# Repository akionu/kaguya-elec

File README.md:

# kaguya-elec

CanSatのための小型電装基板です。第19回能代宇宙イベント出場機体『かぐや』（同志社大学）のために作りました。

- 大幅な小型化を実現しました（当団体比）。42x25mmでここまでできる！
- 安定して動作しています。
- 50mから自由落下しても故障しませんでした（投下1回目）。

ブロック図：

中身としては、RP2040を中心に、電源(DCDC)、無線（LoRa）、センサー（9軸IMU・気圧）、外付けセンサー用コネクタ（GPS・ToF測距）といった感じです。なお、モータードライバは別の基板として分離して使うようにしてあります。

回路図（詳しくはKiCadのデータを参照）：

アートワーク：
表：

裏：

## 『かぐや』について

第19回能代宇宙イベント出場機体『かぐや』（同志社大学）の基板です。
この機体の特徴：
- 成功率向上のため、2機体投下
    - タテに二つ重ねて投下するのでなく、制御性向上のため、ヨコに2つ並べてキャリアに収納
    - そのためのタイヤ展開
- 小型の基板

3回投下した中で、投下2回目の7mが最良の結果でした。実際の状況は大会報告書を参照されたいですが、走破性の不足によるスタックが一番の問題でした（3回ともプログラムは正常に動作・ログ取得）。
- 機体：運営特別賞
- ポスター：能代ロケット実験場　所長賞

なお、この基板で動かしたコードもGitHub上で公開しています。
[リンク](https://github.com/Yudetamago-AM/kaguya-code)

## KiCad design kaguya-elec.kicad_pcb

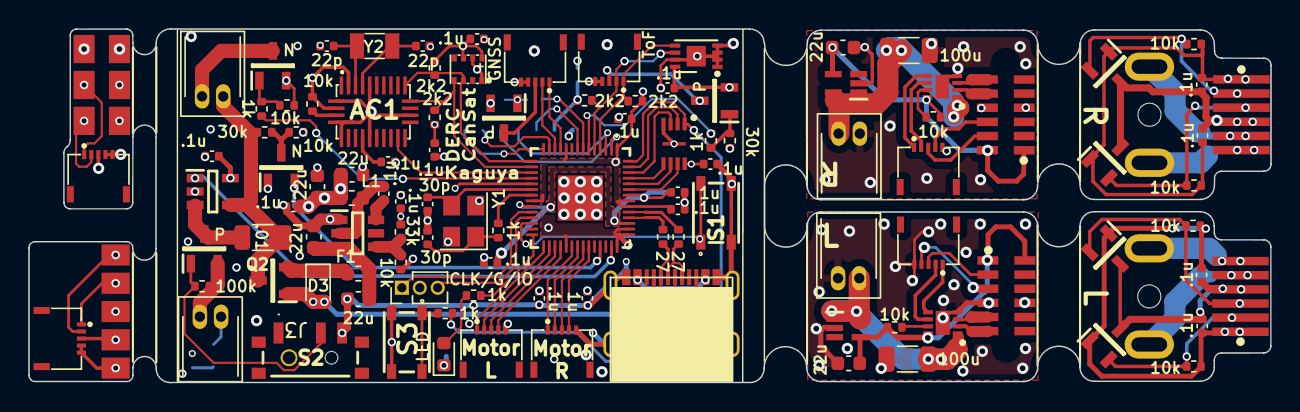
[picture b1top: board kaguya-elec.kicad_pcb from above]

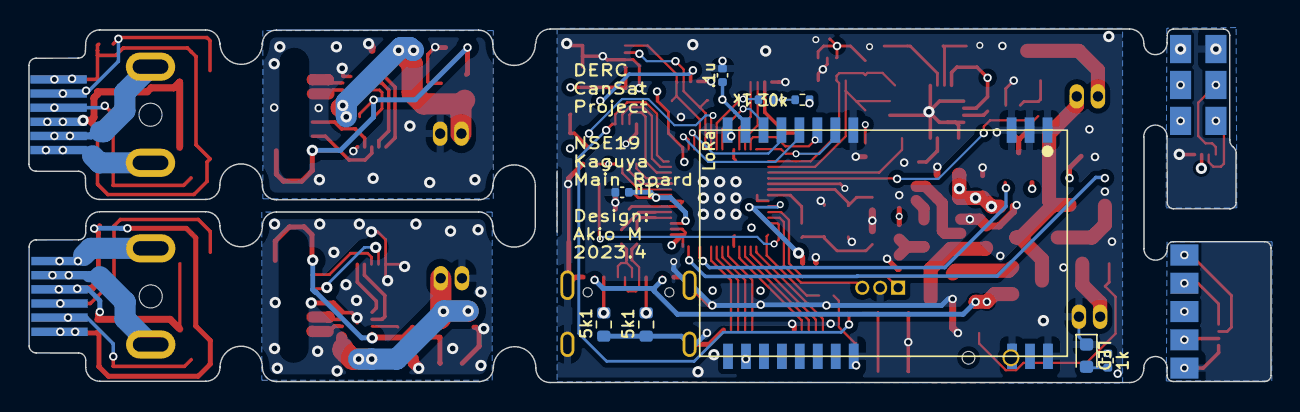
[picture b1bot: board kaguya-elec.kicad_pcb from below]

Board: 4 copper layers, 87.9 x 25.0 mm, 118 parts (9 on the bottom side), 84 nets.

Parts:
AC1: BNO085
C1, C2, C5, C6, C7, C8, C11, C12, C13, C14, C17, C18, C20, C22, C24, C25, C28, C35, C36: 100n; C_0402_1005Metric
C3, C4: 30p; C_0402_1005Metric
C9, C10: 1u; C_0402_1005Metric
C15, C16, C26, C27, C29, C34: 22u; C_0603_1608Metric
C19, C30: 100u; C_1206_3216Metric
C21, C23: 22p; C_0402_1005Metric
D1, D2: LED; LED_0603_1608Metric
D3: CUS10S30; D_SOD-323
F1: BSMD0603-050-9V; Fuse_0603_1608Metric
IC1: RP2040; RP2040TR7
IC2: W25Q16JVUXIQ; SON50P300X200X60-9N
IC3: M24512-DFMC6TG; DFN-8-1EP_3x2mm_P0.5mm_EP1.36x1.46mm
IC4: INA180A2IDBVR; SOT95P280X145-5N
IC5: AP62300TWU-7; SOT95P280X100-6N
IC6, IC11: NJM2878F3-33-TE2; SOT65P210X100-5N
IC7, IC8, IC9, IC10: DRV5013ADQDBZR; SOT95P237X112-3N
IC12, IC14: DRV8837DSGR; SON50P200X200X80-9N
J1: Debug Port; PinHeader_1x03_P1.27mm_Vertical
J2, J3, J10, J15: JST ZH 2; JST ZH 2 Side
J4: ToF; HC-FPC-05-10-5RLTAG
J5: GNSS; HC-FPC-05-10-5RLTAG
J6, J13: B2BL; HC-FPC-05-10-5RLTAG
J7, J14: B2BR; HC-FPC-05-10-5RLTAG
J8: encoderR; encoder connector p-side
J9: encoderL; encoder connector p-side
J11: encoderR; encoder connector e-side
J12: encoderL; encoder connector e-side
J16: ToF_C_P; HC-FPC-05-10-5RLTAG
J17: ToF_C_T; ToF_Flat2
J18: GNSS_C_P; HC-FPC-05-10-5RLTAG
J19: GNSS_C_T; GNSS_Flat
L1: 3.3u; L_0603_1608Metric
M1: Motor_DC_R; motor
M2: Motor_DC_L; motor
Q1, Q4: IRFML8244TRPBF; SOT95P237X112-3N
Q2, Q3, Q5, Q6: IRLML6402; SOT95P237X112-3N
R1, R2, R3, R9, R10, R30, R31: 1k; R_0402_1005Metric
R4, R14, R19, R23, R24, R25, R26, R27, R28, R29: 10k; R_0402_1005Metric
R5, R6: 5.1k; R_0603_1608Metric
R7, R8: 27; R_0402_1005Metric
R11, R12, R15, R16: 2k2; R_0402_1005Metric
R13: 100k; R_0402_1005Metric
R17: 0.01; R_1206_3216Metric
R18, R21, R22: 30k; R_0402_1005Metric
R20: 33.2k; R_0402_1005Metric
S1, S3: SKRPACE010; SMT_4.2X3.2_
S2: SSSS811101
U1: USB_type_C; USB_typeC_t
U2: E220-900T22S-JP; E220-900T22S JP
U3: Goertek_SPL06-001; Goertek SPL06-001
Y1: Crystal_GND24; Crystal_SMD_3225-4Pin_3.2x2.5mm
Y2: 32.768kHz; Crystal_SMD_3215-2Pin_3.2x1.5mm

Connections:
+1V1: C6.1, C8.1, C10.1, IC1.23 (DVDD_1), IC1.45 (VREG_VOUT), IC1.50 (DVDD_2)
+3V3: AC1.3 (VDD), AC1.28 (VDDIO), C1.1, C2.1, C5.1, C7.1, C9.1, C11.1, C12.1, C13.1, C17.1, C18.1, C24.1, C25.1, C26.1, C29.1, IC1.1 (IOVDD_1), IC1.10 (IOVDD_2), IC1.22 (IOVDD_3), IC1.33 (IOVDD_4), IC1.42 (IOVDD_5), IC1.43 (ADC_AVDD), IC1.44 (VREG_VIN), IC1.48 (USB_VDD), IC1.49 (IOVDD_6), IC2.8 (VCC), IC3.8 (VCC), IC4.5 (VS), L1.2, Q4.1 (G), Q5.2, Q6.2, R10.1, R11.1, R12.1, R14.2, R15.1, R16.1, R20.2, R21.1, R22.1, U2.10 (VCC), U3.6 (VDDIO), U3.8 (VDD)
+BATT: C19.1, C30.1, IC4.4 (IN-), IC6.1 (CONTROL), IC6.5 (VIN), IC11.1 (CONTROL), IC11.5 (VIN), IC12.1 (VM), IC14.1 (VM), J2.2, J10.2, J15.2, Q2.3, R17.1, R18.1
/3V3A: C20.1, C27.1, C28.1, C34.1, C35.1, C36.1, IC6.4 (VOUT), IC7.1 (VCC), IC8.1 (VCC), IC9.1 (VCC), IC10.1 (VCC), IC11.4 (VOUT), IC12.8 (VCC), IC14.8 (VCC), J8.1, J9.1, J11.1, J12.1, R24.1, R25.2, R26.1, R27.1, R28.2, R29.1
/C_GNSS_RX: J18.1, J19.2
/C_GNSS_TX: J18.2, J19.1
/C_GNSS_VCC: J18.3, J19.4
/C_TOF_SCL: J16.2, J17.2
/C_TOF_SDA: J16.1, J17.4
/C_TOF_VCC: J16.3, J17.5
/QSPI_SCLK: IC1.52 (QSPI_SCLK), IC2.6 (CLK)
/QSPI_SD0: IC1.53 (QSPI_SD0), IC2.5 (DI_(IO0))
/QSPI_SD1: IC1.55 (QSPI_SD1), IC2.2 (DO_(IO1))
/QSPI_SD2: IC1.54 (QSPI_SD2), IC2.3 (~WP_(IO2))
/QSPI_SD3: IC1.51 (QSPI_SD3), IC2.7 (~HOLD_OR_RESET_(IO3))
/QSPI_SS: IC1.56 (QSPI_SS_N), IC2.1 (~CS), R2.2
/USB_BD_N: IC1.46 (USB_DM), R8.1
/USB_BD_P: IC1.47 (USB_DP), R7.1
/USB_D_N: R8.2, U1.5 (B7_DN2), U1.7 (A7_DN1)
/USB_D_P: R7.2, U1.6 (A6_DP1), U1.8 (B6_DP2)
/motor_L1: IC14.3 (OUT2), J9.5, J12.5, M2.1 (+)
/motor_L2: IC14.2 (OUT1), J9.6, J12.6, M2.2 (-)
/motor_R1: IC12.2 (OUT1), J8.5, J11.5, M1.1 (+)
/motor_R2: IC12.3 (OUT2), J8.6, J11.6, M1.2 (-)
BNO085_INTN: AC1.14 (H_INTN), IC1.17 (GPIO14)
GND: AC1.2 (GND_1), AC1.5 (PS1), AC1.6 (PS0/WAKE), AC1.10 (CLKSEL0), AC1.17 (SA0/H_MOSI), AC1.25 (GND_2), C1.2, C2.2, C3.1, C4.1, C5.2, C6.2, C7.2, C8.2, C9.2, C10.2, C11.2, C12.2, C13.2, C14.2, C15.2, C16.2, C17.2, C18.2, C19.2, C20.2, C21.2, C23.2, C24.2, C25.2, C26.2, C27.2, C28.2, C29.2, C30.2, C34.2, C35.2, C36.2, D1.1 (K), D2.1 (K), IC1.19 (TESTEN), IC1.57 (GND), IC2.4 (GND), IC2.9 (EP), IC3.1 (E0), IC3.2 (E1), IC3.3 (E2), IC3.4 (VSS), IC3.7 (~WC), IC3.9 (EP), IC4.2 (GND), IC5.1 (GND), IC6.2 (GND), IC7.3 (GND), IC8.3 (GND), IC9.3 (GND), IC10.3 (GND), IC11.2 (GND), IC12.4 (GND), IC12.9 (EP), IC14.4 (GND), IC14.9 (EP), J1.2, J3.1, J4.4, J4.5, J5.4, J5.5, J6.5, J7.5, J8.4, J9.4, J10.1, J11.4, J12.4, J13.5, J14.5, J15.1, J16.4, J16.5, J17.6, J18.4, J18.5, J19.5, Q1.2 (S), R4.2, R5.2, R6.2, R19.2, R23.1, S1.3, S1.4, S2.3, S3.3, S3.4, U1.1 (A1-B12_GND), U1.12 (A12-B1_GND), U1.SHIELD, U2.1 (GND), U2.2 (GND), U2.3 (GND), U2.4 (GND), U2.11 (GND), U2.13 (GND), U2.19 (GND), U2.20 (GND), U2.22 (GND), U3.1 (GND), U3.7 (GND), Y1.2, Y1.4
GNSS_RX: IC1.11 (GPIO8), J5.1
GNSS_TX: IC1.12 (GPIO9), J5.2
GNSS_VCC: IC1.7 (GPIO5), R30.1
I2C0_SCL: AC1.19 (H_SCL/SCK/RX), IC1.16 (GPIO13), R12.2, U3.4 (SCK)
I2C0_SDA: AC1.20 (H_SDA/H_MISO/TX), IC1.15 (GPIO12), R11.2, U3.3 (SDA)
I2C1_SCL: IC1.5 (GPIO3), IC3.6 (SCL), J4.2, R15.2
I2C1_SDA: IC1.4 (GPIO2), IC3.5 (SDA), J4.1, R16.2
Imonitor_Main: IC1.41 (GPIO29/ADC3), IC4.1 (OUT)
LED: IC1.28 (GPIO17), R9.1
LORA_AUX: IC1.8 (GPIO6), U2.9 (AUX)
LORA_M0: IC1.14 (GPIO11), U2.5 (M0)
LORA_M1: IC1.13 (GPIO10), U2.6 (M1)
LORA_RX: IC1.2 (GPIO0), U2.7 (RXD)
LORA_TX: IC1.3 (GPIO1), U2.8 (TXD)
MOE_LA: IC1.31 (GPIO20), IC7.2 (OUT), J6.3, J9.2, J12.2, J13.3, R27.2
MOE_LB: IC1.32 (GPIO21), IC8.2 (OUT), J6.4, J9.3, J12.3, J13.4, R29.2
MOE_RA: IC1.36 (GPIO24), IC9.2 (OUT), J7.3, J8.2, J11.2, J14.3, R25.1
MOE_RB: IC1.37 (GPIO25), IC10.2 (OUT), J7.4, J8.3, J11.3, J14.4, R28.1
M_LA: IC1.29 (GPIO18), IC14.5 (IN2), J6.1, J13.1
M_LB: IC1.30 (GPIO19), IC14.6 (IN1), J6.2, J13.2
M_RA: IC1.34 (GPIO22), IC12.5 (IN2), J7.1, J14.1
M_RB: IC1.35 (GPIO23), IC12.6 (IN1), J7.2, J14.2
unnamed: AC1.4 (BOOTN), R14.1
unnamed: AC1.9 (CAP), C14.1
unnamed: AC1.26 (XOUT32/CLKSEL1), C23.1, Y2.2
unnamed: AC1.27 (XIN32), C21.1, Y2.1
unnamed: C4.2, R3.1, Y1.1
unnamed: C15.1, C16.1, F1.2, IC5.3 (VIN)
unnamed: C22.1, IC5.2 (SW), L1.1
unnamed: C22.2, IC5.6 (BST)
unnamed: D1.2 (A), R9.2
unnamed: D2.2 (A), R10.2
unnamed: D3.1 (K), F1.1, Q2.2
unnamed: IC4.3 (IN+), Q3.3, R17.2
unnamed: IC5.4 (FB), R20.1, R23.2
unnamed: IC12.7 (NSLEEP), R24.2
unnamed: IC14.7 (NSLEEP), R26.2
unnamed: J2.1, Q1.3 (D)
unnamed: J3.2, Q3.2, R13.1
unnamed: J4.3, Q5.3
unnamed: J5.3, Q6.3
unnamed: Q1.1 (G), R1.2, R4.1
unnamed: Q3.1, R13.2, S2.2
unnamed: Q4.3 (D), R18.2, R19.1
unnamed: Q5.1, R21.2, R31.2
unnamed: Q6.1, R22.2, R30.2
unnamed: R2.1, S3.1, S3.2
unnamed: R5.1, U1.4 (A5_CC1)
unnamed: R6.1, U1.10 (B5_CC2)
Nichrome: IC1.18 (GPIO15), R1.1
RUN: IC1.26 (RUN), S1.1, S1.2
SWCLK: IC1.24 (SWCLK), J1.1
SWDIO: IC1.25 (SWDIO), J1.3
ToF_VCC: IC1.6 (GPIO4), R31.1
VBUS: D3.2 (A), Q2.1, U1.2 (A4-B9_VBUS), U1.11 (A9-B4_VBUS)
Vmonitor: IC1.39 (GPIO27/ADC1), Q4.2 (S)
XIN: C3.2, IC1.20 (XIN), Y1.3
XOUT: IC1.21 (XOUT), R3.2

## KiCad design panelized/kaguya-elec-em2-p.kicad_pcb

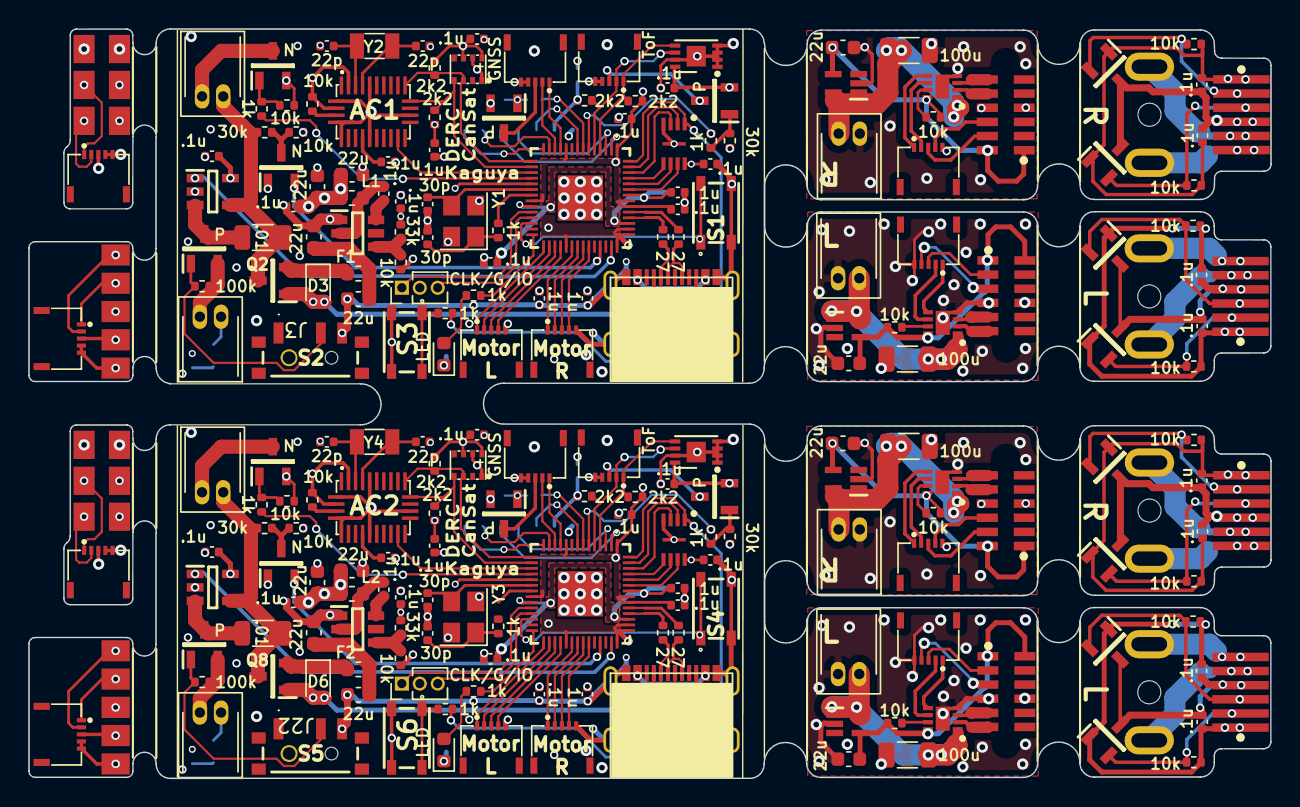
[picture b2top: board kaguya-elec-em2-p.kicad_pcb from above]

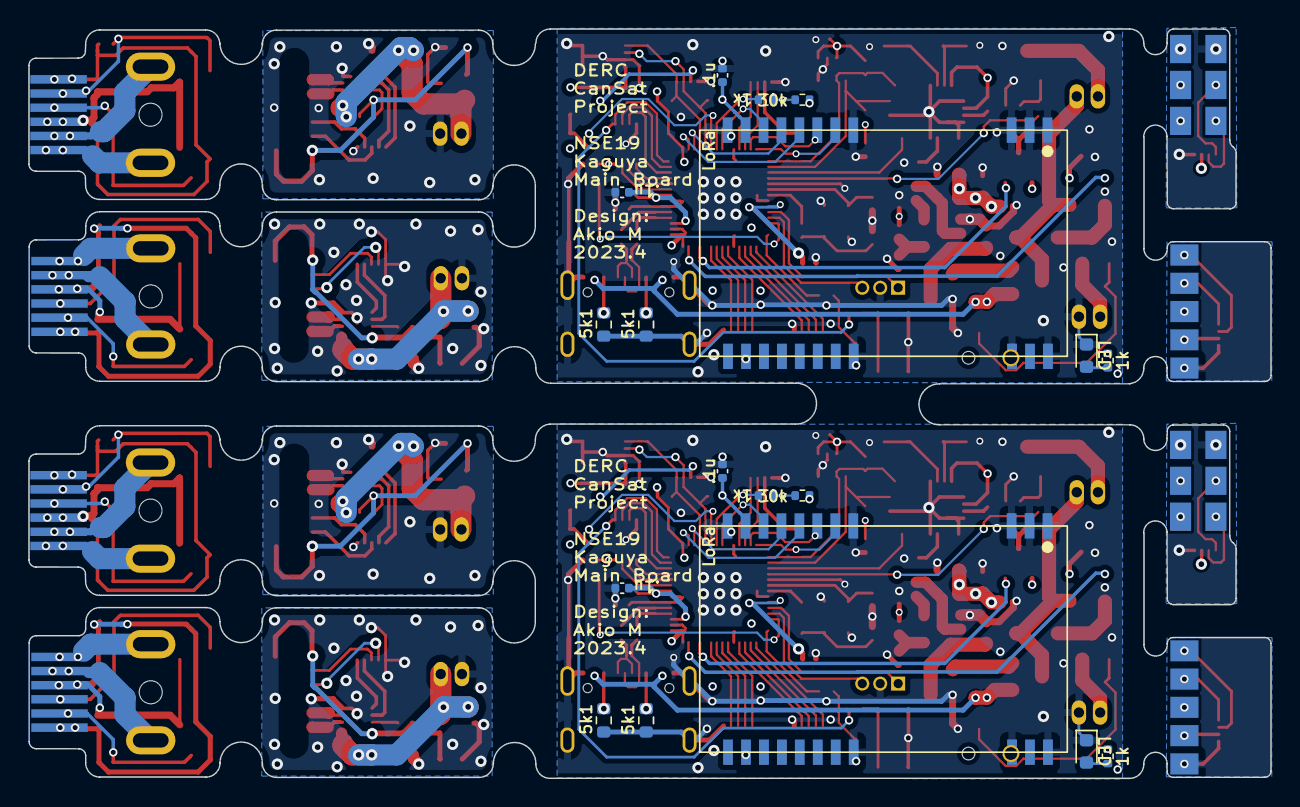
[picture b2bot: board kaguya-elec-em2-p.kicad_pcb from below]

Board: 4 copper layers, 87.9 x 53.0 mm, 236 parts (18 on the bottom side), 84 nets.

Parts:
AC1, AC2: BNO085
C1, C2, C5, C6, C7, C8, C11, C12, C13, C14, C17, C18, C20, C22, C24, C25, C28, C31, C32, C35, C36, C38, C39, C40, C41, C44, C45, C46, C47, C50, C51, C53, C55, C57, C58, C61, C65, C66: 100n; C_0402_1005Metric
C3, C4, C33, C37: 30p; C_0402_1005Metric
C9, C10, C42, C43: 1u; C_0402_1005Metric
C15, C16, C26, C27, C29, C34, C48, C49, C59, C60, C62, C64: 22u; C_0603_1608Metric
C19, C30, C52, C63: 100u; C_1206_3216Metric
C21, C23, C54, C56: 22p; C_0402_1005Metric
D1, D2, D4, D5: LED; LED_0603_1608Metric
D3, D6: CUS10S30; D_SOD-323
F1, F2: BSMD0603-050-9V; Fuse_0603_1608Metric
IC1, IC13: RP2040; RP2040TR7
IC2, IC15: W25Q16JVUXIQ; SON50P300X200X60-9N
IC3, IC16: M24512-DFMC6TG; DFN-8-1EP_3x2mm_P0.5mm_EP1.36x1.46mm
IC4, IC17: INA180A2IDBVR; SOT95P280X145-5N
IC5, IC18: AP62300TWU-7; SOT95P280X100-6N
IC6, IC11, IC19, IC24: NJM2878F3-33-TE2; SOT65P210X100-5N
IC7, IC8, IC9, IC10, IC20, IC21, IC22, IC23: DRV5013ADQDBZR; SOT95P237X112-3N
IC12, IC14, IC25, IC26: DRV8837DSGR; SON50P200X200X80-9N
J1, J20: Debug Port; PinHeader_1x03_P1.27mm_Vertical
J2, J3, J10, J15, J21, J22, J29, J34: JST ZH 2; JST ZH 2 Side
J4, J23: ToF; HC-FPC-05-10-5RLTAG
J5, J24: GNSS; HC-FPC-05-10-5RLTAG
J6, J13, J25, J32: B2BL; HC-FPC-05-10-5RLTAG
J7, J14, J26, J33: B2BR; HC-FPC-05-10-5RLTAG
J8, J27: encoderR; encoder connector p-side
J9, J28: encoderL; encoder connector p-side
J11, J30: encoderR; encoder connector e-side
J12, J31: encoderL; encoder connector e-side
J16, J35: ToF_C_P; HC-FPC-05-10-5RLTAG
J17, J36: ToF_C_T; ToF_Flat2
J18, J37: GNSS_C_P; HC-FPC-05-10-5RLTAG
J19, J38: GNSS_C_T; GNSS_Flat
L1, L2: 3.3u; L_0603_1608Metric
M1, M3: Motor_DC_R; motor
M2, M4: Motor_DC_L; motor
Q1, Q4, Q7, Q10: IRFML8244TRPBF; SOT95P237X112-3N
Q2, Q3, Q5, Q6, Q8, Q9, Q11, Q12: IRLML6402; SOT95P237X112-3N
R1, R2, R3, R9, R10, R30, R31, R32, R33, R34, R40, R41, R61, R62: 1k; R_0402_1005Metric
R4, R14, R19, R23, R24, R25, R26, R27, R28, R29, R35, R45, R50, R54, R55, R56, R57, R58, R59, R60: 10k; R_0402_1005Metric
R5, R6, R36, R37: 5.1k; R_0603_1608Metric
R7, R8, R38, R39: 27; R_0402_1005Metric
R11, R12, R15, R16, R42, R43, R46, R47: 2k2; R_0402_1005Metric
R13, R44: 100k; R_0402_1005Metric
R17, R48: 0.01; R_1206_3216Metric
R18, R21, R22, R49, R52, R53: 30k; R_0402_1005Metric
R20, R51: 33.2k; R_0402_1005Metric
S1, S3, S4, S6: SKRPACE010; SMT_4.2X3.2_
S2, S5: SSSS811101
U1, U4: USB_type_C; USB_typeC_t
U2, U5: E220-900T22S-JP; E220-900T22S JP
U3, U6: Goertek_SPL06-001; Goertek SPL06-001
Y1, Y3: Crystal_GND24; Crystal_SMD_3225-4Pin_3.2x2.5mm
Y2, Y4: 32.768kHz; Crystal_SMD_3215-2Pin_3.2x1.5mm

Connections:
+1V1: C6.1, C8.1, C10.1, C39.1, C41.1, C43.1, IC1.23 (DVDD_1), IC1.45 (VREG_VOUT), IC1.50 (DVDD_2), IC13.23 (DVDD_1), IC13.45 (VREG_VOUT), IC13.50 (DVDD_2)
+3V3: AC1.3 (VDD), AC1.28 (VDDIO), AC2.3 (VDD), AC2.28 (VDDIO), C1.1, C2.1, C5.1, C7.1, C9.1, C11.1, C12.1, C13.1, C17.1, C18.1, C24.1, C25.1, C26.1, C29.1, C31.1, C32.1, C38.1, C40.1, C42.1, C44.1, C45.1, C46.1, C50.1, C51.1, C57.1, C58.1, C59.1, C62.1, IC1.1 (IOVDD_1), IC1.10 (IOVDD_2), IC1.22 (IOVDD_3), IC1.33 (IOVDD_4), IC1.42 (IOVDD_5), IC1.43 (ADC_AVDD), IC1.44 (VREG_VIN), IC1.48 (USB_VDD), IC1.49 (IOVDD_6), IC2.8 (VCC), IC3.8 (VCC), IC4.5 (VS), IC13.1 (IOVDD_1), IC13.10 (IOVDD_2), IC13.22 (IOVDD_3), IC13.33 (IOVDD_4), IC13.42 (IOVDD_5), IC13.43 (ADC_AVDD), IC13.44 (VREG_VIN), IC13.48 (USB_VDD), IC13.49 (IOVDD_6), IC15.8 (VCC), IC16.8 (VCC), IC17.5 (VS), L1.2, L2.2, Q4.1 (G), Q5.2, Q6.2, Q10.1 (G), Q11.2, Q12.2, R10.1, R11.1, R12.1, R14.2, R15.1, R16.1, R20.2, R21.1, R22.1, R41.1, R42.1, R43.1, R45.2, R46.1, R47.1, R51.2, R52.1, R53.1, U2.10 (VCC), U3.6 (VDDIO), U3.8 (VDD), U5.10 (VCC), U6.6 (VDDIO), U6.8 (VDD)
+BATT: C19.1, C30.1, C52.1, C63.1, IC4.4 (IN-), IC6.1 (CONTROL), IC6.5 (VIN), IC11.1 (CONTROL), IC11.5 (VIN), IC12.1 (VM), IC14.1 (VM), IC17.4 (IN-), IC19.1 (CONTROL), IC19.5 (VIN), IC24.1 (CONTROL), IC24.5 (VIN), IC25.1 (VM), IC26.1 (VM), J2.2, J10.2, J15.2, J21.2, J29.2, J34.2, Q2.3, Q8.3, R17.1, R18.1, R48.1, R49.1
/3V3A: C20.1, C27.1, C28.1, C34.1, C35.1, C36.1, C53.1, C60.1, C61.1, C64.1, C65.1, C66.1, IC6.4 (VOUT), IC7.1 (VCC), IC8.1 (VCC), IC9.1 (VCC), IC10.1 (VCC), IC11.4 (VOUT), IC12.8 (VCC), IC14.8 (VCC), IC19.4 (VOUT), IC20.1 (VCC), IC21.1 (VCC), IC22.1 (VCC), IC23.1 (VCC), IC24.4 (VOUT), IC25.8 (VCC), IC26.8 (VCC), J8.1, J9.1, J11.1, J12.1, J27.1, J28.1, J30.1, J31.1, R24.1, R25.2, R26.1, R27.1, R28.2, R29.1, R55.1, R56.2, R57.1, R58.1, R59.2, R60.1
/C_GNSS_RX: J18.1, J19.2, J37.1, J38.2
/C_GNSS_TX: J18.2, J19.1, J37.2, J38.1
/C_GNSS_VCC: J18.3, J19.4, J37.3, J38.4
/C_TOF_SCL: J16.2, J17.2, J35.2, J36.2
/C_TOF_SDA: J16.1, J17.4, J35.1, J36.4
/C_TOF_VCC: J16.3, J17.5, J35.3, J36.5
/QSPI_SCLK: IC1.52 (QSPI_SCLK), IC2.6 (CLK), IC13.52 (QSPI_SCLK), IC15.6 (CLK)
/QSPI_SD0: IC1.53 (QSPI_SD0), IC2.5 (DI_(IO0)), IC13.53 (QSPI_SD0), IC15.5 (DI_(IO0))
/QSPI_SD1: IC1.55 (QSPI_SD1), IC2.2 (DO_(IO1)), IC13.55 (QSPI_SD1), IC15.2 (DO_(IO1))
/QSPI_SD2: IC1.54 (QSPI_SD2), IC2.3 (~WP_(IO2)), IC13.54 (QSPI_SD2), IC15.3 (~WP_(IO2))
/QSPI_SD3: IC1.51 (QSPI_SD3), IC2.7 (~HOLD_OR_RESET_(IO3)), IC13.51 (QSPI_SD3), IC15.7 (~HOLD_OR_RESET_(IO3))
/QSPI_SS: IC1.56 (QSPI_SS_N), IC2.1 (~CS), IC13.56 (QSPI_SS_N), IC15.1 (~CS), R2.2, R33.2
/USB_BD_N: IC1.46 (USB_DM), IC13.46 (USB_DM), R8.1, R39.1
/USB_BD_P: IC1.47 (USB_DP), IC13.47 (USB_DP), R7.1, R38.1
/USB_D_N: R8.2, R39.2, U1.5 (B7_DN2), U1.7 (A7_DN1), U4.5 (B7_DN2), U4.7 (A7_DN1)
/USB_D_P: R7.2, R38.2, U1.6 (A6_DP1), U1.8 (B6_DP2), U4.6 (A6_DP1), U4.8 (B6_DP2)
/motor_L1: IC14.3 (OUT2), IC26.3 (OUT2), J9.5, J12.5, J28.5, J31.5, M2.1 (+), M4.1 (+)
/motor_L2: IC14.2 (OUT1), IC26.2 (OUT1), J9.6, J12.6, J28.6, J31.6, M2.2 (-), M4.2 (-)
/motor_R1: IC12.2 (OUT1), IC25.2 (OUT1), J8.5, J11.5, J27.5, J30.5, M1.1 (+), M3.1 (+)
/motor_R2: IC12.3 (OUT2), IC25.3 (OUT2), J8.6, J11.6, J27.6, J30.6, M1.2 (-), M3.2 (-)
BNO085_INTN: AC1.14 (H_INTN), AC2.14 (H_INTN), IC1.17 (GPIO14), IC13.17 (GPIO14)
GND: AC1.2 (GND_1), AC1.5 (PS1), AC1.6 (PS0/WAKE), AC1.10 (CLKSEL0), AC1.17 (SA0/H_MOSI), AC1.25 (GND_2), AC2.2 (GND_1), AC2.5 (PS1), AC2.6 (PS0/WAKE), AC2.10 (CLKSEL0), AC2.17 (SA0/H_MOSI), AC2.25 (GND_2), C1.2, C2.2, C3.1, C4.1, C5.2, C6.2, C7.2, C8.2, C9.2, C10.2, C11.2, C12.2, C13.2, C14.2, C15.2, C16.2, C17.2, C18.2, C19.2, C20.2, C21.2, C23.2, C24.2, C25.2, C26.2, C27.2, C28.2, C29.2, C30.2, C31.2, C32.2, C33.1, C34.2, C35.2, C36.2, C37.1, C38.2, C39.2, C40.2, C41.2, C42.2, C43.2, C44.2, C45.2, C46.2, C47.2, C48.2, C49.2, C50.2, C51.2, C52.2, C53.2, C54.2, C56.2, C57.2, C58.2, C59.2, C60.2, C61.2, C62.2, C63.2, C64.2, C65.2, C66.2, D1.1 (K), D2.1 (K), D4.1 (K), D5.1 (K), IC1.19 (TESTEN), IC1.57 (GND), IC2.4 (GND), IC2.9 (EP), IC3.1 (E0), IC3.2 (E1), IC3.3 (E2), IC3.4 (VSS), IC3.7 (~WC), IC3.9 (EP), IC4.2 (GND), IC5.1 (GND), IC6.2 (GND), IC7.3 (GND), IC8.3 (GND), IC9.3 (GND), IC10.3 (GND), IC11.2 (GND), IC12.4 (GND), IC12.9 (EP), IC13.19 (TESTEN), IC13.57 (GND), IC14.4 (GND), IC14.9 (EP), IC15.4 (GND), IC15.9 (EP), IC16.1 (E0), IC16.2 (E1), IC16.3 (E2), IC16.4 (VSS), IC16.7 (~WC), IC16.9 (EP), IC17.2 (GND), IC18.1 (GND), IC19.2 (GND), IC20.3 (GND), IC21.3 (GND), IC22.3 (GND), IC23.3 (GND), IC24.2 (GND), IC25.4 (GND), IC25.9 (EP), IC26.4 (GND), IC26.9 (EP), J1.2, J3.1, J4.4, J4.5, J5.4, J5.5, J6.5, J7.5, J8.4, J9.4, J10.1, J11.4, J12.4, J13.5, J14.5, J15.1, J16.4, J16.5, J17.6, J18.4, J18.5, J19.5, J20.2, J22.1, J23.4, J23.5, J24.4, J24.5, J25.5, J26.5, J27.4, J28.4, J29.1, J30.4, J31.4, J32.5, J33.5, J34.1, J35.4, J35.5, J36.6, J37.4, J37.5, J38.5, Q1.2 (S), Q7.2 (S), R4.2, R5.2, R6.2, R19.2, R23.1, R35.2, R36.2, R37.2, R50.2, R54.1, S1.3, S1.4, S2.3, S3.3, S3.4, S4.3, S4.4, S5.3, S6.3, S6.4, U1.1 (A1-B12_GND), U1.12 (A12-B1_GND), U1.SHIELD, U2.1 (GND), U2.2 (GND), U2.3 (GND), U2.4 (GND), U2.11 (GND), U2.13 (GND), U2.19 (GND), U2.20 (GND), U2.22 (GND), U3.1 (GND), U3.7 (GND), U4.1 (A1-B12_GND), U4.12 (A12-B1_GND), U4.SHIELD, U5.1 (GND), U5.2 (GND), U5.3 (GND), U5.4 (GND), U5.11 (GND), U5.13 (GND), U5.19 (GND), U5.20 (GND), U5.22 (GND), U6.1 (GND), U6.7 (GND), Y1.2, Y1.4, Y3.2, Y3.4
GNSS_RX: IC1.11 (GPIO8), IC13.11 (GPIO8), J5.1, J24.1
GNSS_TX: IC1.12 (GPIO9), IC13.12 (GPIO9), J5.2, J24.2
GNSS_VCC: IC1.7 (GPIO5), IC13.7 (GPIO5), R30.1, R61.1
I2C0_SCL: AC1.19 (H_SCL/SCK/RX), AC2.19 (H_SCL/SCK/RX), IC1.16 (GPIO13), IC13.16 (GPIO13), R12.2, R43.2, U3.4 (SCK), U6.4 (SCK)
I2C0_SDA: AC1.20 (H_SDA/H_MISO/TX), AC2.20 (H_SDA/H_MISO/TX), IC1.15 (GPIO12), IC13.15 (GPIO12), R11.2, R42.2, U3.3 (SDA), U6.3 (SDA)
I2C1_SCL: IC1.5 (GPIO3), IC3.6 (SCL), IC13.5 (GPIO3), IC16.6 (SCL), J4.2, J23.2, R15.2, R46.2
I2C1_SDA: IC1.4 (GPIO2), IC3.5 (SDA), IC13.4 (GPIO2), IC16.5 (SDA), J4.1, J23.1, R16.2, R47.2
Imonitor_Main: IC1.41 (GPIO29/ADC3), IC4.1 (OUT), IC13.41 (GPIO29/ADC3), IC17.1 (OUT)
LED: IC1.28 (GPIO17), IC13.28 (GPIO17), R9.1, R40.1
LORA_AUX: IC1.8 (GPIO6), IC13.8 (GPIO6), U2.9 (AUX), U5.9 (AUX)
LORA_M0: IC1.14 (GPIO11), IC13.14 (GPIO11), U2.5 (M0), U5.5 (M0)
LORA_M1: IC1.13 (GPIO10), IC13.13 (GPIO10), U2.6 (M1), U5.6 (M1)
LORA_RX: IC1.2 (GPIO0), IC13.2 (GPIO0), U2.7 (RXD), U5.7 (RXD)
LORA_TX: IC1.3 (GPIO1), IC13.3 (GPIO1), U2.8 (TXD), U5.8 (TXD)
MOE_LA: IC1.31 (GPIO20), IC7.2 (OUT), IC13.31 (GPIO20), IC20.2 (OUT), J6.3, J9.2, J12.2, J13.3, J25.3, J28.2, J31.2, J32.3, R27.2, R58.2
MOE_LB: IC1.32 (GPIO21), IC8.2 (OUT), IC13.32 (GPIO21), IC21.2 (OUT), J6.4, J9.3, J12.3, J13.4, J25.4, J28.3, J31.3, J32.4, R29.2, R60.2
MOE_RA: IC1.36 (GPIO24), IC9.2 (OUT), IC13.36 (GPIO24), IC22.2 (OUT), J7.3, J8.2, J11.2, J14.3, J26.3, J27.2, J30.2, J33.3, R25.1, R56.1
MOE_RB: IC1.37 (GPIO25), IC10.2 (OUT), IC13.37 (GPIO25), IC23.2 (OUT), J7.4, J8.3, J11.3, J14.4, J26.4, J27.3, J30.3, J33.4, R28.1, R59.1
M_LA: IC1.29 (GPIO18), IC13.29 (GPIO18), IC14.5 (IN2), IC26.5 (IN2), J6.1, J13.1, J25.1, J32.1
M_LB: IC1.30 (GPIO19), IC13.30 (GPIO19), IC14.6 (IN1), IC26.6 (IN1), J6.2, J13.2, J25.2, J32.2
M_RA: IC1.34 (GPIO22), IC12.5 (IN2), IC13.34 (GPIO22), IC25.5 (IN2), J7.1, J14.1, J26.1, J33.1
M_RB: IC1.35 (GPIO23), IC12.6 (IN1), IC13.35 (GPIO23), IC25.6 (IN1), J7.2, J14.2, J26.2, J33.2
unnamed: AC1.4 (BOOTN), AC2.4 (BOOTN), R14.1, R45.1
unnamed: AC1.9 (CAP), AC2.9 (CAP), C14.1, C47.1
unnamed: AC1.26 (XOUT32/CLKSEL1), AC2.26 (XOUT32/CLKSEL1), C23.1, C56.1, Y2.2, Y4.2
unnamed: AC1.27 (XIN32), AC2.27 (XIN32), C21.1, C54.1, Y2.1, Y4.1
unnamed: C4.2, C37.2, R3.1, R34.1, Y1.1, Y3.1
unnamed: C15.1, C16.1, C48.1, C49.1, F1.2, F2.2, IC5.3 (VIN), IC18.3 (VIN)
unnamed: C22.1, C55.1, IC5.2 (SW), IC18.2 (SW), L1.1, L2.1
unnamed: C22.2, C55.2, IC5.6 (BST), IC18.6 (BST)
unnamed: D1.2 (A), D4.2 (A), R9.2, R40.2
unnamed: D2.2 (A), D5.2 (A), R10.2, R41.2
unnamed: D3.1 (K), D6.1 (K), F1.1, F2.1, Q2.2, Q8.2
unnamed: IC4.3 (IN+), IC17.3 (IN+), Q3.3, Q9.3, R17.2, R48.2
unnamed: IC5.4 (FB), IC18.4 (FB), R20.1, R23.2, R51.1, R54.2
unnamed: IC12.7 (NSLEEP), IC25.7 (NSLEEP), R24.2, R55.2
unnamed: IC14.7 (NSLEEP), IC26.7 (NSLEEP), R26.2, R57.2
unnamed: J2.1, J21.1, Q1.3 (D), Q7.3 (D)
unnamed: J3.2, J22.2, Q3.2, Q9.2, R13.1, R44.1
unnamed: J4.3, J23.3, Q5.3, Q11.3
unnamed: J5.3, J24.3, Q6.3, Q12.3
unnamed: Q1.1 (G), Q7.1 (G), R1.2, R4.1, R32.2, R35.1
unnamed: Q3.1, Q9.1, R13.2, R44.2, S2.2, S5.2
unnamed: Q4.3 (D), Q10.3 (D), R18.2, R19.1, R49.2, R50.1
unnamed: Q5.1, Q11.1, R21.2, R31.2, R52.2, R62.2
unnamed: Q6.1, Q12.1, R22.2, R30.2, R53.2, R61.2
unnamed: R2.1, R33.1, S3.1, S3.2, S6.1, S6.2
unnamed: R5.1, R36.1, U1.4 (A5_CC1), U4.4 (A5_CC1)
unnamed: R6.1, R37.1, U1.10 (B5_CC2), U4.10 (B5_CC2)
Nichrome: IC1.18 (GPIO15), IC13.18 (GPIO15), R1.1, R32.1
RUN: IC1.26 (RUN), IC13.26 (RUN), S1.1, S1.2, S4.1, S4.2
SWCLK: IC1.24 (SWCLK), IC13.24 (SWCLK), J1.1, J20.1
SWDIO: IC1.25 (SWDIO), IC13.25 (SWDIO), J1.3, J20.3
ToF_VCC: IC1.6 (GPIO4), IC13.6 (GPIO4), R31.1, R62.1
VBUS: D3.2 (A), D6.2 (A), Q2.1, Q8.1, U1.2 (A4-B9_VBUS), U1.11 (A9-B4_VBUS), U4.2 (A4-B9_VBUS), U4.11 (A9-B4_VBUS)
Vmonitor: IC1.39 (GPIO27/ADC1), IC13.39 (GPIO27/ADC1), Q4.2 (S), Q10.2 (S)
XIN: C3.2, C33.2, IC1.20 (XIN), IC13.20 (XIN), Y1.3, Y3.3
XOUT: IC1.21 (XOUT), IC13.21 (XOUT), R3.2, R34.2

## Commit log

2023-03-19 add major parts
2023-03-19 add pcb
2023-03-21 update pcb
2023-03-21 improve artwork
2023-03-26 em-1 done
2023-03-27 remove blind vias
2023-04-06 fix erattas on em-1
2023-07-06 final ver
2023-10-13 add README
2023-11-10 Create LICENSE
